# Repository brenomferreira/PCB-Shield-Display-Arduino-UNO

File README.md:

# PCB-Shield-Display-Arduino-UNO
Shield Display Arduino UNO

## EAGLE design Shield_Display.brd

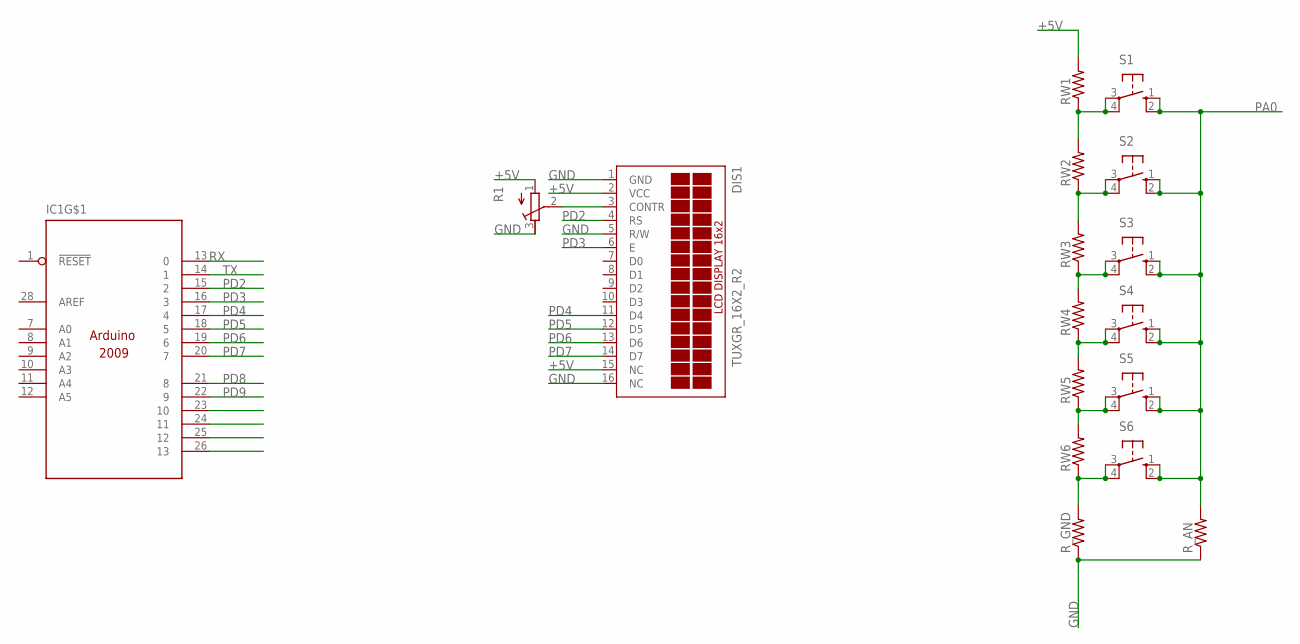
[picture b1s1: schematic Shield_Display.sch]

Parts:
DIS1: TUXGR_16X2_R2
IC1: ARDUINO2009_22; ARDUINO2009_2
R1: R-TRIMM64W; RTRIM64W
RW1, RW2, RW3, RW4, RW5, RW6: R-US_0204/7; 0204/7
R_AN: R-US_0204/7; 0204/7
R_GND: R-US_0204/7; 0204/7
S1, S2, S3, S4, S5, S6: 10-XX; B3F-10XX

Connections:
+3V3: IC1.2 (+3V3)
+5V: DIS1.2 (VCC), DIS1.15 (NC), IC1.3 (+5V), R1.1 (A), RW1.2
+VIN: IC1.6 (+VIN)
GND: DIS1.1 (GND), DIS1.5 (R/W), DIS1.16 (NC), IC1.4 (GND), IC1.5 (GND), IC1.27 (GND), R1.3 (E), R_AN.1, R_GND.1
unnamed: DIS1.3 (CONTR), R1.2 (S)
unnamed: RW1.1, RW2.2, S1.3, S1.4 (P1)
unnamed: RW2.1, RW3.2, S2.3, S2.4 (P1)
unnamed: RW3.1, RW4.2, S3.3, S3.4 (P1)
unnamed: RW4.1, RW5.2, S4.3, S4.4 (P1)
unnamed: RW5.1, RW6.2, S5.3, S5.4 (P1)
unnamed: RW6.1, R_GND.2, S6.3, S6.4 (P1)
PA0: R_AN.2, S1.1 (S), S1.2 (S1), S2.1 (S), S2.2 (S1), S3.1 (S), S3.2 (S1), S4.1 (S), S4.2 (S1), S5.1 (S), S5.2 (S1), S6.1 (S), S6.2 (S1)
PD2: DIS1.4 (RS), IC1.15 (2)
PD3: DIS1.6 (E), IC1.16 (3)
PD4: DIS1.11 (D4), IC1.17 (4)
PD5: DIS1.12 (D5), IC1.18 (5)
PD6: DIS1.13 (D6), IC1.19 (6)
PD7: DIS1.14 (D7), IC1.20 (7)
PD8: IC1.21 (8)
PD9: IC1.22 (9)
RX: IC1.13 (0)
TX: IC1.14 (1)

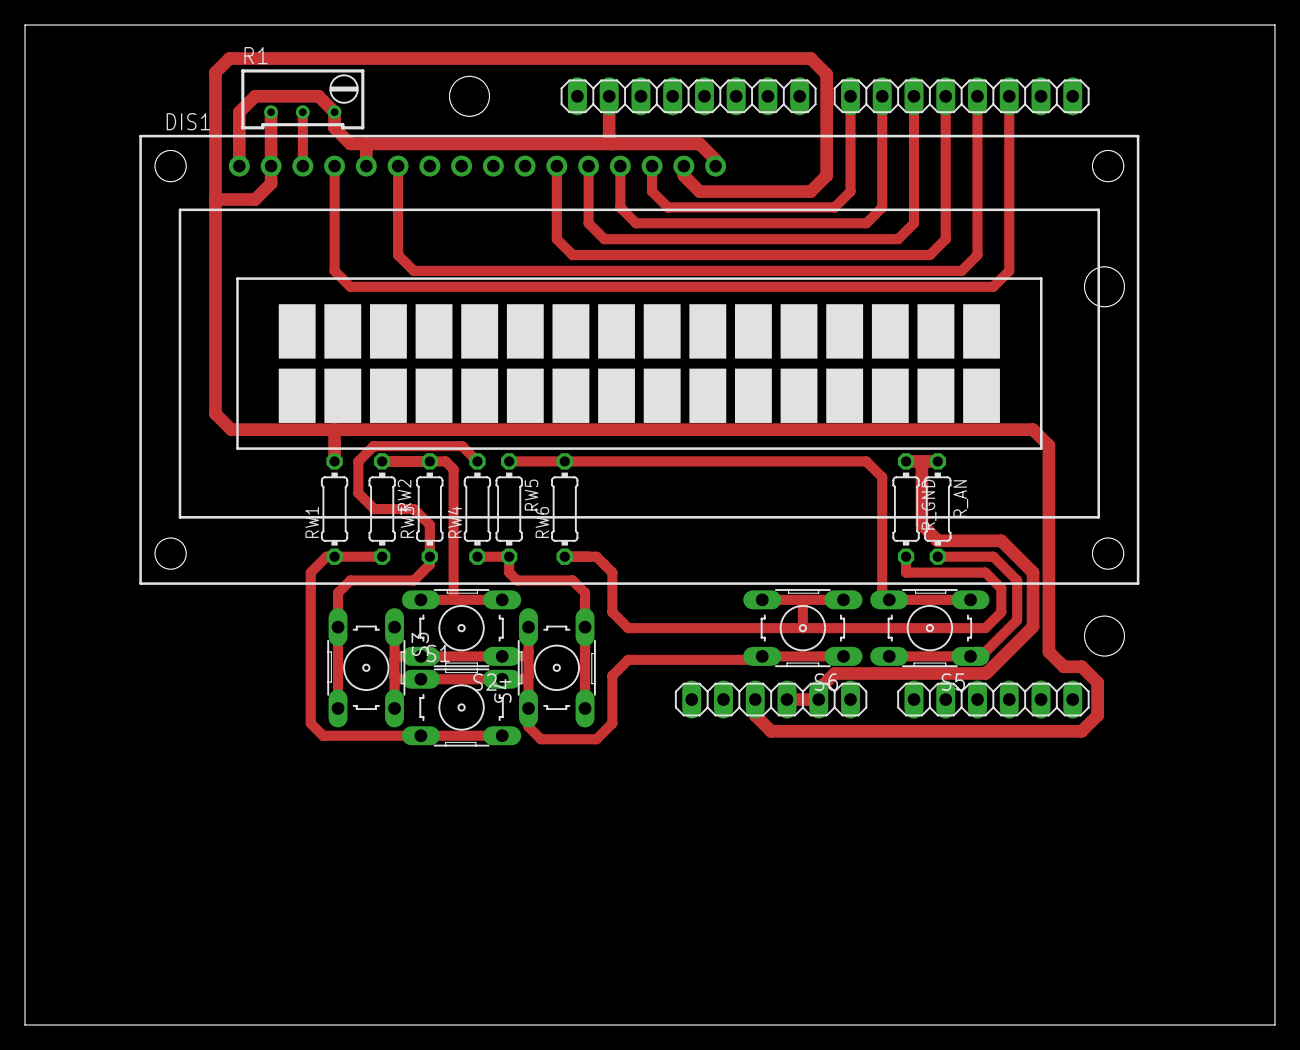
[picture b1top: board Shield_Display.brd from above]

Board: 2 copper layers, 100.0 x 80.0 mm, 17 parts (0 on the bottom side), 16 nets.

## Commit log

2018-06-13 primeiro commit para v.0.0 no gitHub
2018-06-14 add PDFs
